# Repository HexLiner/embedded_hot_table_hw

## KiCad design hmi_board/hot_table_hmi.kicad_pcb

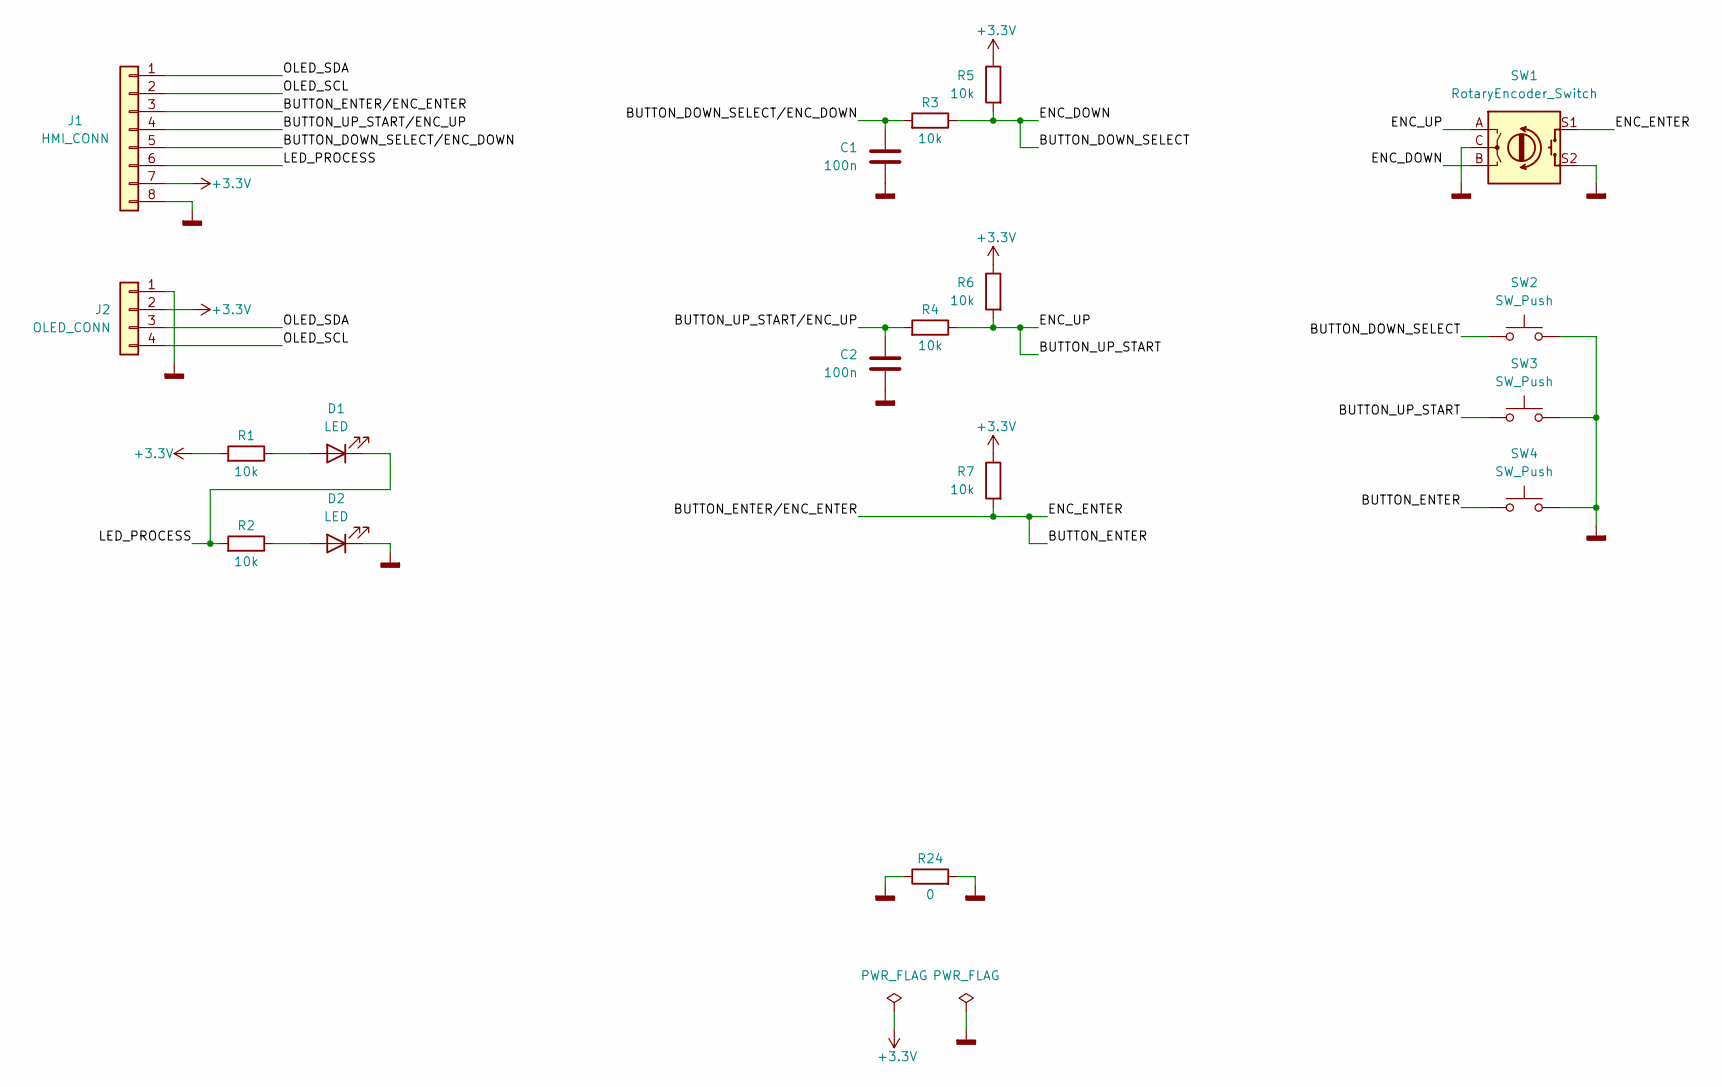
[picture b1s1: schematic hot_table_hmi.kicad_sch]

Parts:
C1, C2: 100n; C_0805_2012Metric
D1, D2: LED; LED_D3.0mm_Clear
J1: HMI_CONN; PinHeader_1x08_P2.54mm_Horizontal
J2: OLED_CONN; PinHeader_1x04_P2.54mm_Vertical
R1: 10k; R_1206_3216Metric
R2, R3, R4, R5, R6, R7: 10k; R_0805_2012Metric
R24: 0; R_1206_3216Metric
SW1: RotaryEncoder_Switch; RotaryEncoder_Alps_EC11E-Switch_Vertical_H20mm
SW2, SW3, SW4: SW_Push; SW_PUSH_6mm

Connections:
+3V3: J1.7, J2.2, R1.2, R5.1, R6.1, R7.1
/BUTTON_DOWN_START: R3.1, R5.2, SW1.B, SW2.1
/BUTTON_DOWN_START/ENC_DOWN: C1.1, J1.5, R3.2
/BUTTON_ENTER: J1.3, R7.2, SW1.S1, SW4.1
/BUTTON_UP_SELECT/ENC_UP: C2.1, J1.4, R4.2
/ENC_UP: R4.1, R6.2, SW1.A, SW3.1
/LED_PROCESS: D1.1 (K), J1.6, R2.2
/OLED_SCL: J1.2, J2.4
/OLED_SDA: J1.1, J2.3
GNDD: C1.2, C2.2, D2.1 (K), J1.8, J2.1, R24.1, R24.2, SW1.C, SW1.S2, SW2.2, SW3.2, SW4.2
unnamed: D1.2 (A), R1.1
unnamed: D2.2 (A), R2.1

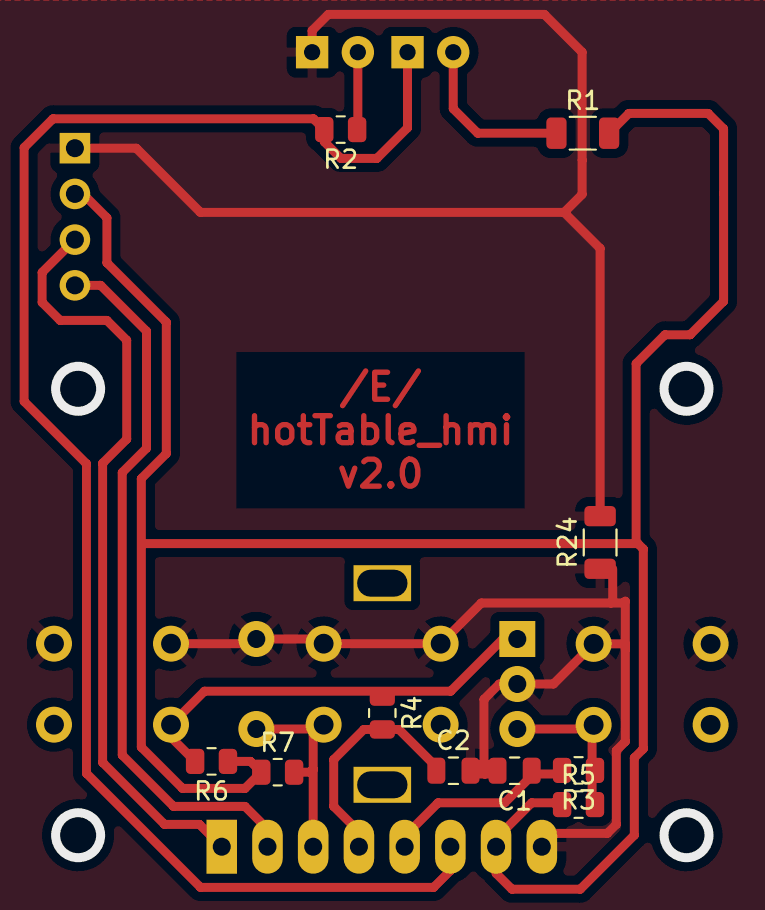
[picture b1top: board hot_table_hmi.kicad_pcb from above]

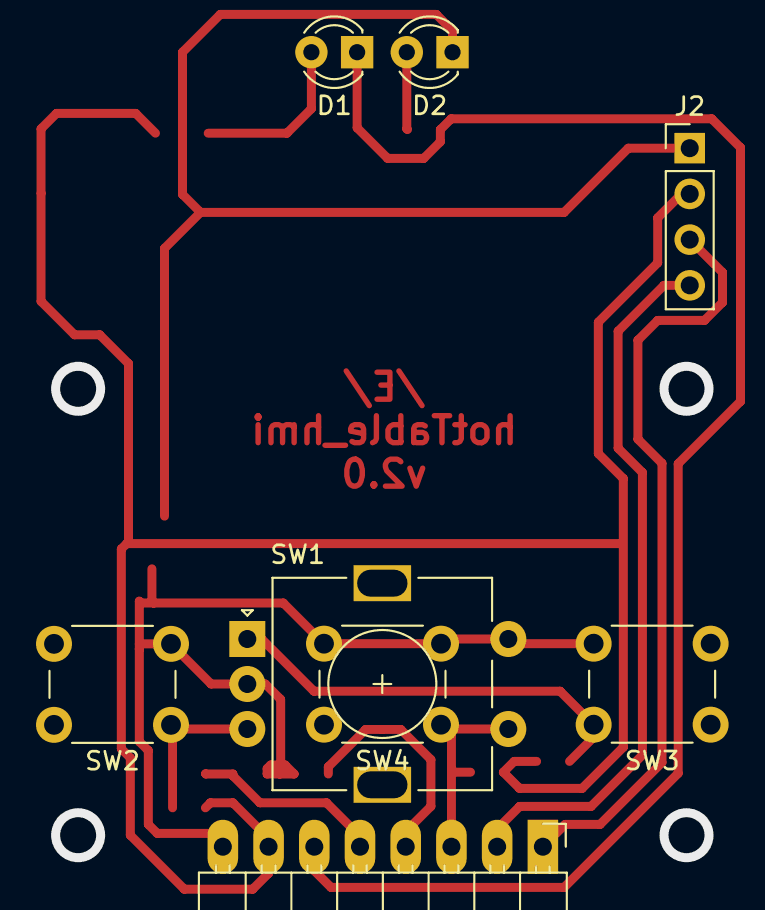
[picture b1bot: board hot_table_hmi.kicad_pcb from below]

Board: 2 copper layers, 18 parts (8 on the bottom side), 12 nets.

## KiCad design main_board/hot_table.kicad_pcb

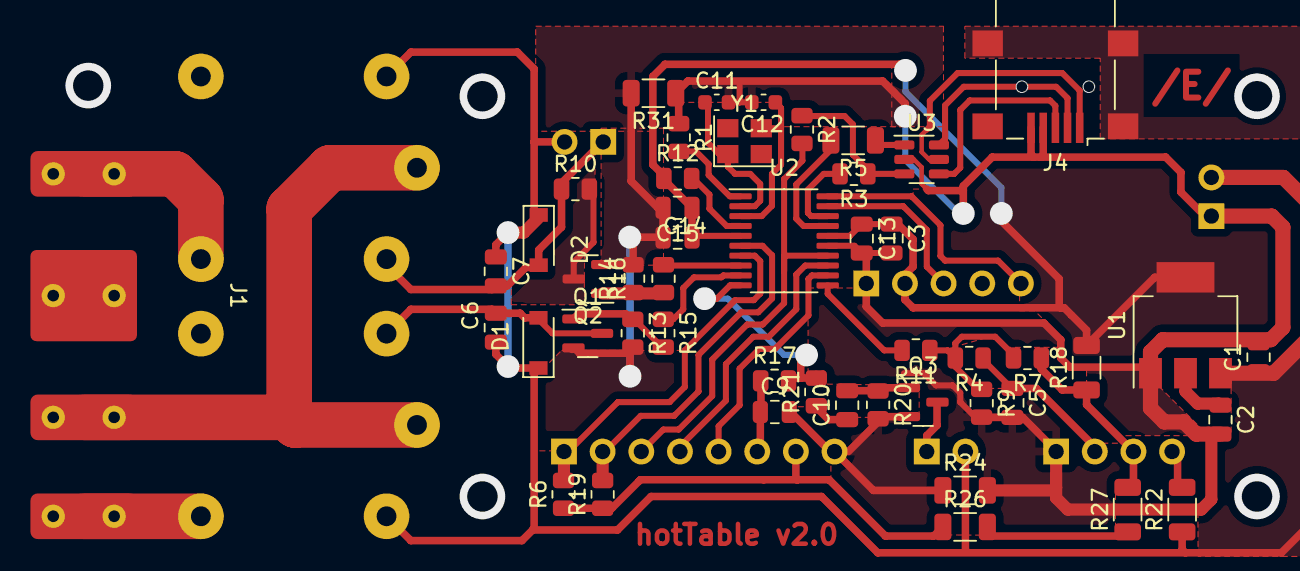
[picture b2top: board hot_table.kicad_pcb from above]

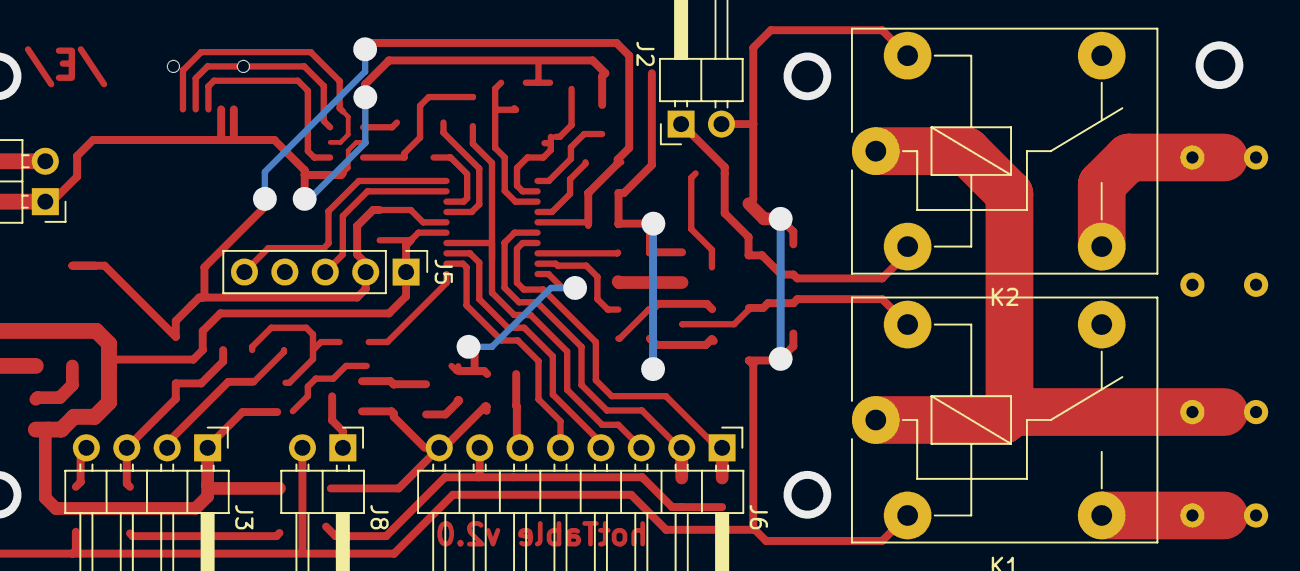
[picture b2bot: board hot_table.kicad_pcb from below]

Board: 2 copper layers, 57 parts (8 on the bottom side), 39 nets.

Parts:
C1, C2, C3, C5, C6, C7, C9, C10, C14: 100n; C_0805_2012Metric
C11, C12: 22p; C_0603_1608Metric
C13: 4.7u; C_0805_2012Metric
C15: 1u; C_0805_2012Metric
D1, D2: 1N4448W; D_SOD-123
J1: HV_CONN; my_4pin_220v_conn
J2: FUN_12V_CONN; PinHeader_1x02_P2.54mm_Horizontal
J3: T_CONTROL_CONN; PinHeader_1x04_P2.54mm_Horizontal
J4: USB_B_Mini; USB_Mini-B_Lumberg_2486_01_Horizontal
J5: SWD_CONN; PinHeader_1x05_P2.54mm_Vertical
J6: HMI_CONN; PinHeader_1x08_P2.54mm_Horizontal
J7: PSU_12V_CONN; PinHeader_1x02_P2.54mm_Horizontal
J8: BUZZER_CONN; PinHeader_1x02_P2.54mm_Horizontal
K1, K2: FINDER-36.11; Relay_SPDT_Finder_36.11
Q1, Q2, Q3: MMBT3904; SOT-23
R1, R2, R3, R4, R6, R7, R11, R12, R15, R16, R17, R19, R21: 10k; R_0805_2012Metric
R5: 10k; R_1206_3216Metric
R9, R10, R13, R14, R20: 1k; R_0805_2012Metric
R18, R22, R24, R26, R27, R31: 0; R_1206_3216Metric
U1: AMS1117-3.3; SOT-223-3_TabPin2
U2: STM32F070F6Px; TSSOP-20_4.4x6.5mm_P0.65mm
U3: USBLC6-2SC6; SOT-23-6
Y1: Crystal_GND24; Crystal_SMD_Abracon_ABM8G-4Pin_3.2x2.5mm

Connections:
+3V3: C2.1, C3.1, C13.1, C14.1, C15.1, J3.3, J5.2, J6.7, R6.1, R7.1, R12.1, R18.1, R18.2, R19.1, R26.1, R26.2, R27.1, R27.2, U1.2 (VO), U2.5 (VDDA), U2.16 (VDD)
+12V: C1.1, C6.1, C7.1, D1.1 (K), D2.1 (K), J2.2, J3.4, J7.2, J8.2, K1.A1, K2.A2, R22.1, R22.2, U1.3 (VI)
/220V_P: J1.3, K1.11, K2.11
/BUTTON_DOWN_SELECT/ENC_DOWN: J6.5, U2.12 (PA6)
/BUTTON_UP_START/ENC_UP: J6.4, U2.13 (PA7)
/BUZZER: J8.1, Q3.3 (C)
/FUN_EN: R16.1, U2.8 (PA2)
/FUN_EN_12V: C7.2, D2.2 (A), J2.1, K2.A1, R10.1
/FUN_EN_220V: J1.1, K2.14
/HEATER_EN: R15.1, U2.9 (PA3)
/HEATER_EN_220V: J1.4, K1.14
/LED_PROCESS: C9.1, J6.6, R17.1
/LED_PROCESS/BUZZER: R17.2, R21.2, U2.10 (PA4)
/OLED_SCL: J6.2, R19.2, U2.6 (PA0)
/OLED_SDA: J6.1, R6.2, U2.7 (PA1)
/RESET: R12.2, U2.4 (NRST)
/SWCLK: J5.5, U2.20 (PA14(SWCLK))
/SWDIO: J5.3, U2.19 (PA13(SWDIO))
/T_CONTROL: R11.2, U2.11 (PA5)
/USB_DM: R5.2, U2.17 (PA9/PA11)
/USB_DP: R3.2, U2.18 (PA10/PA12)
/USB_PUP/BUTTON_ENTER/ENC_ENTER: J6.3, U2.14 (PB1)
GNDD: C1.2, C2.2, C3.2, C5.2, C9.2, C11.2, C12.2, C13.2, C14.2, C15.2, J3.1, J4.4 (ID), J4.5 (GND), J5.1, J6.8, J7.1, Q1.2 (E), Q2.2 (E), Q3.2 (E), R1.1, R9.2, R13.2, R14.2, R20.2, R24.1, R24.2, R31.1, R31.2, U1.1 (GND), U2.15 (VSS), U3.2 (GND)
unnamed: C5.1, J3.2, R4.1
unnamed: C6.2, D1.2 (A), K1.A2, Q1.3 (C)
unnamed: C10.1, R21.1
unnamed: C10.2, Q3.1 (B), R20.1
unnamed: C11.1, U2.2 (PF0(OSC_IN)), Y1.1
unnamed: C12.1, U2.3 (PF1(OSC_OUT)), Y1.3
unnamed: J4.1 (VBUS), U3.5 (VBUS)
unnamed: J4.2 (D-), U3.6 (I/O1)
unnamed: J4.3 (D+), U3.4 (I/O2)
unnamed: Q1.1 (B), R13.1, R15.2
unnamed: Q2.1 (B), R14.1, R16.2
unnamed: Q2.3 (C), R10.2
unnamed: R1.2, U2.1 (BOOT0)
unnamed: R2.1, R3.1, U3.3 (I/O2)
unnamed: R5.1, U3.1 (I/O1)
unnamed: R4.2, R7.2, R9.1, R11.1

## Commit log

2025-03-16 Initial
2025-09-18 Change comment
